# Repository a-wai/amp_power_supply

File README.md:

# Amplifier power supply

A generic power supply PCB for tube amplifiers, suitable for both fixed bias
and cathode bias amplifiers.

### Copyright

Copyright 2019, Arnaud Ferraris.

This documentation describes Open Hardware and is licensed under the
CERN OHL v.1.2.

You may redistribute and modify this documentation under the terms of the
[CERN OHL v.1.2](http://ohwr.org/cernohl). This documentation is distributed
WITHOUT ANY EXPRESS OR IMPLIED WARRANTY, INCLUDING OF MERCHANTABILITY,
SATISFACTORY QUALITY AND FITNESS FOR A PARTICULAR PURPOSE.

Please see the CERN OHL v.1.2 for applicable conditions.

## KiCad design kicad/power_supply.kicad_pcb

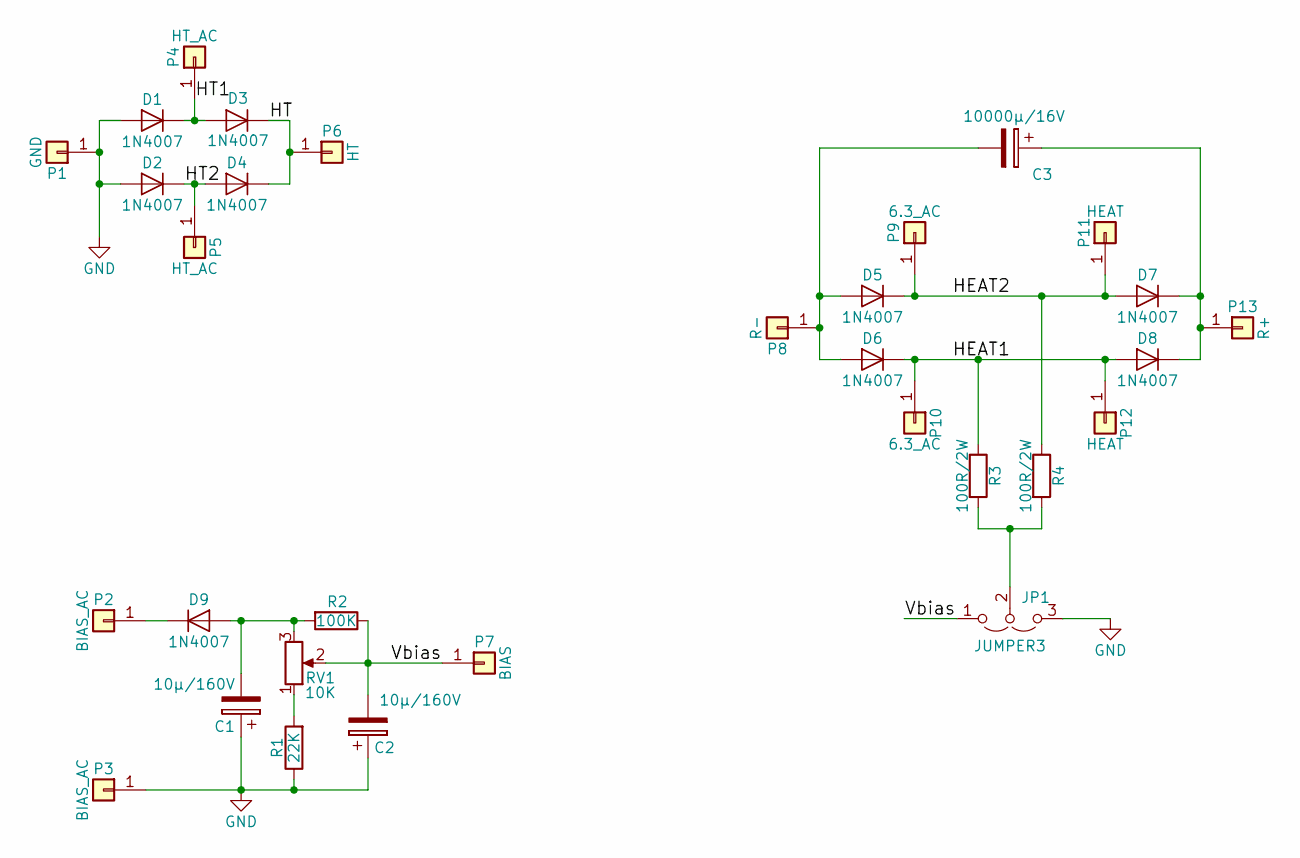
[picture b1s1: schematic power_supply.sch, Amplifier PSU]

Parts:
C1, C2: 10µ/160V; CP_Axial_L18.0mm_D10.0mm_P25.00mm_Horizontal
C3: 10000µ/16V; CP_Radial_D26.0mm_P10.00mm_SnapIn; MPN B41303J4109M
D1, D2, D3, D4, D5, D6, D7, D8, D9: 1N4007; D_DO-41_SOD81_P7.62mm_Horizontal
JP1: JUMPER3; PinHeader_1x03_P2.54mm_Vertical
P1: GND; TURRET
P2, P3: BIAS_AC; TURRET
P4, P5: HT_AC; TURRET
P6: HT; TURRET
P7: BIAS; TURRET
P8: R-; TURRET
P9, P10: 6.3_AC; TURRET
P11, P12: HEAT; TURRET
P13: R+; TURRET
R1: 22K; R_Axial_DIN0309_L9.0mm_D3.2mm_P12.70mm_Horizontal; MPN 273-22K-RC
R2: 100K; R_Axial_DIN0309_L9.0mm_D3.2mm_P12.70mm_Horizontal; MPN 273-100K-RC
R3, R4: 100R/2W; R_Axial_DIN0414_L11.9mm_D4.5mm_P15.24mm_Horizontal; MPN PO593-0-5-100
RV1: 10K; Potentiometer_Piher_PT-15-V02_Vertical; MPN PT15

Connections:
/HEAT1: D6.1 (K), D8.2 (A), P10.1, P12.1, R3.1
/HEAT2: D5.1 (K), D7.2 (A), P9.1, P11.1, R4.1
/HT: D3.1 (K), D4.1 (K), P6.1
/HT1: D1.1 (K), D3.2 (A), P4.1
/HT2: D2.1 (K), D4.2 (A), P5.1
/Vbias: C2.2, JP1.1 (A), P7.1, R2.1, RV1.2; also elsewhere on the board
GND: C1.1, C2.1, D1.2 (A), D2.2 (A), JP1.3 (B), P1.1, P3.1, R1.1
unnamed: C1.2, D9.2 (A), R2.2, RV1.3
unnamed: C3.1, D7.1 (K), D8.1 (K), P13.1
unnamed: C3.2, D5.2 (A), D6.2 (A), P8.1
unnamed: D9.1 (K), P2.1
unnamed: JP1.2 (C), R3.2, R4.2
unnamed: R1.2, RV1.1

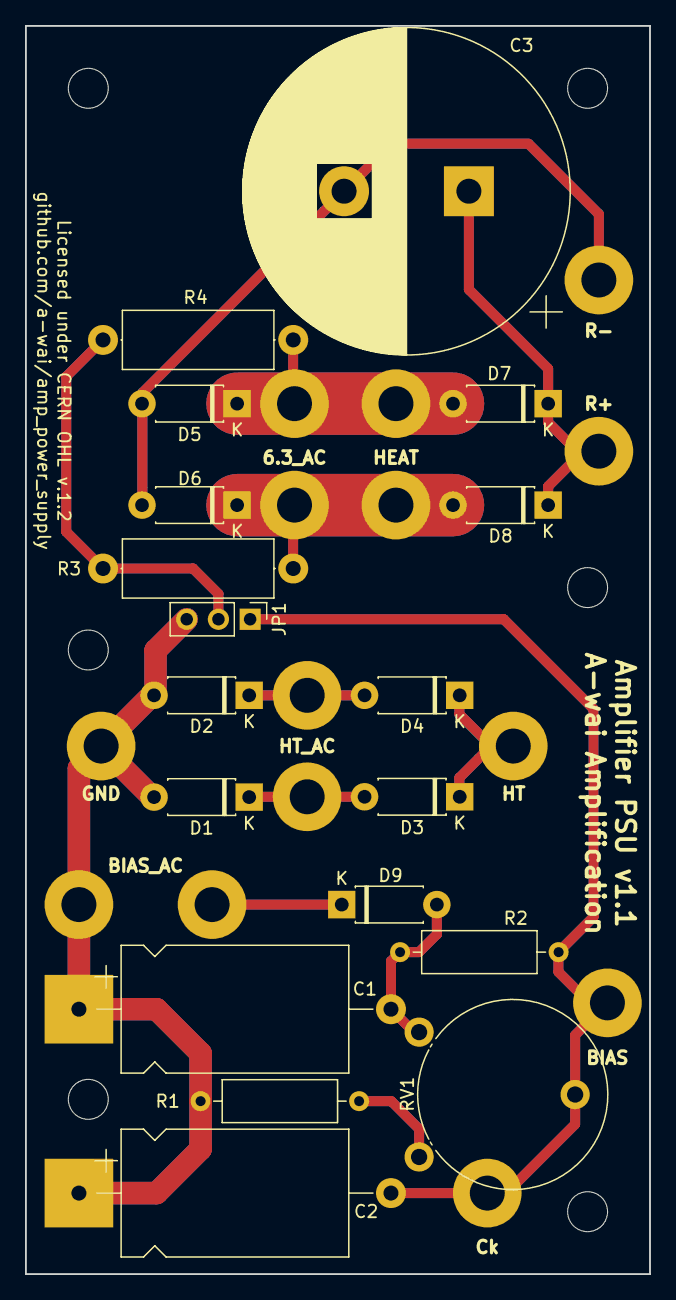
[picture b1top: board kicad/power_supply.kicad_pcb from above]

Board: 2 copper layers, 50.0 x 100.0 mm, 32 parts (0 on the bottom side), 13 nets.

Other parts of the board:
T1: Ck; TURRET

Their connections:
/Vbias: T1.1; also elsewhere on the board

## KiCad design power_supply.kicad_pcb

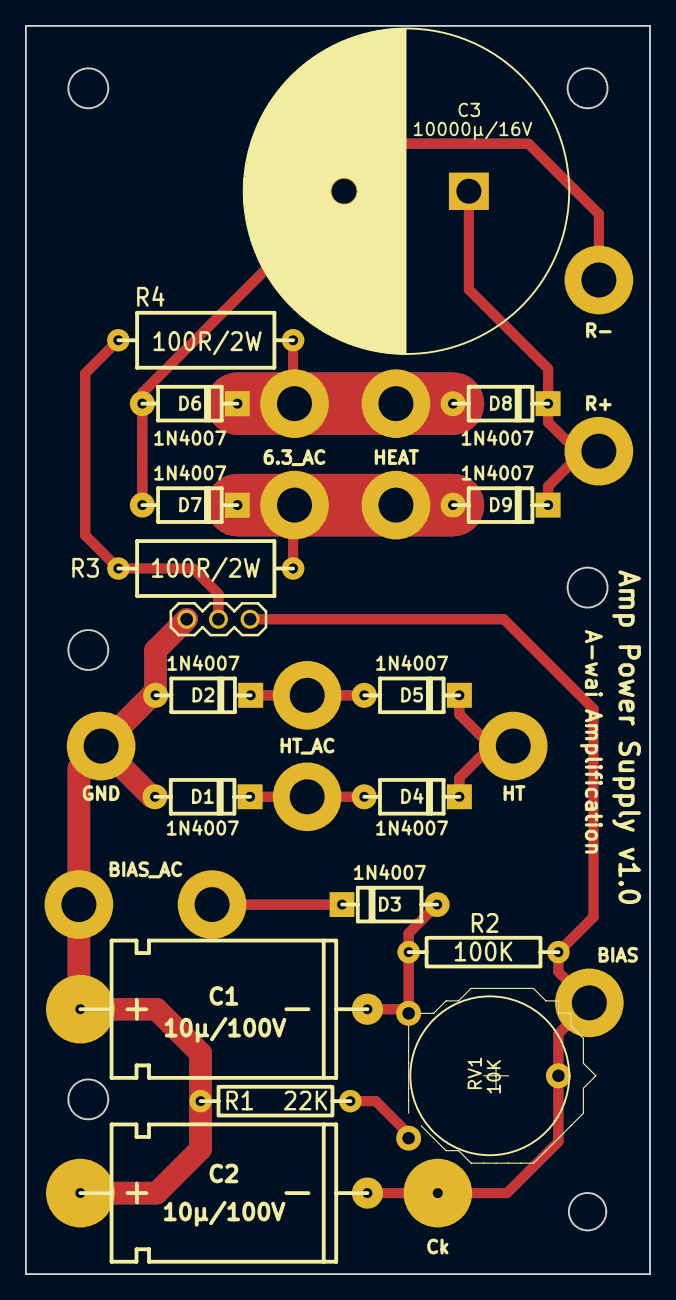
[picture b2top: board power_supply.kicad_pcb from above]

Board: 2 copper layers, 50.0 x 100.0 mm, 32 parts (0 on the bottom side), 13 nets.

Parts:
C1, C2: 10µ/100V; CPA_10µF_160V
C3: 10000µ/16V; C_Radial_D26_L31_P10
D1, D2, D3, D4, D5, D6, D7, D8, D9: 1N4007; DIODE
JP1: JUMPER3; 1X03
P1: GND; TURRET
P2, P3: BIAS_AC; TURRET
P4, P5: HT_AC; TURRET
P6: HT; TURRET
P7: BIAS; TURRET
P8: R-; TURRET
P9, P10: 6.3_AC; TURRET
P11, P12: HEAT; TURRET
P13: R+; TURRET
R1: 22K; R_0.5W
R2: 100K; R_0.5W
R3, R4: 100R/2W; R_2W
RV1: 10K; Potentiometer_Trimmer-Piher_PT15-V12-5_horizontal
T1: Ck; TURRET

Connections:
/HEAT1: D7.1, D9.2, P10.1, P12.1, R3.1
/HEAT2: D6.1, D8.2, P9.1, P11.1, R4.1
/HT: D4.1, D5.1, P6.1
/HT1: D1.1, D4.2, P4.1
/HT2: D2.1, D5.2, P5.1
/Vbias: C2.2, JP1.1, P7.1, R2.1, RV1.2, T1.1
GND: C1.1, C2.1, D1.2, D2.2, JP1.3, P1.1, P3.1, R1.1
unnamed: C1.2, D3.2, R2.2, RV1.1
unnamed: C3.1, D8.1, D9.1, P13.1
unnamed: C3.2, D6.2, D7.2, P8.1
unnamed: D3.1, P2.1
unnamed: JP1.2, R3.2, R4.2
unnamed: R1.2, RV1.3

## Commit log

2016-08-25 Initial import
2016-08-25 Add LICENSE file
2016-08-25 Add license info to README
2016-09-08 Update track widths & route on both layers
2016-11-09 Fix tracks near fixation hole & pot too close to bias turret
2016-11-09 Regenerate drill file & add project name
2019-03-13 Update for KiCAD v5
2019-03-13 Move design files to a subfolder + add full license documentation
2019-03-13 Add BOM + PDF schematics
2019-03-14 Fix project name in README

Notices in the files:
kicad/power_supply.kicad_pcb:
Licensed under CERN OHL v.1.2
